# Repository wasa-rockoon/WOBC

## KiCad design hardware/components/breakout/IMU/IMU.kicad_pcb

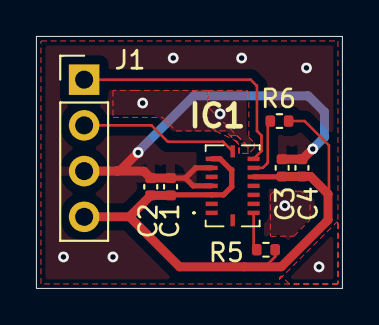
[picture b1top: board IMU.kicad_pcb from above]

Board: 2 copper layers, 17.0 x 14.0 mm, 8 parts (0 on the bottom side), 6 nets.

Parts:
C1, C3: 10μF; C_0402_1005Metric
C2, C4: 100nF; C_0402_1005Metric
IC1: BMI088
J1: Conn_01x04_Pin; PinHeader_1x04_P2.54mm_Vertical
R5, R6: 4.7K; R_0402_1005Metric

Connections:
AD0: IC1.15 (SDO1), R5.1
AD1: IC1.10 (SDO2), R6.1
GND: C1.2, C2.2, C3.2, C4.2, IC1.4 (GNDA), IC1.6 (GNDIO), J1.3
SCL: IC1.8 (SCL/SCK), J1.2
SDA: IC1.9 (SDA/SDI), J1.1
VDD: C1.1, C2.1, C3.1, C4.1, IC1.3 (VDD), IC1.7 (PS), IC1.11 (VDDIO), J1.4, R5.2, R6.2

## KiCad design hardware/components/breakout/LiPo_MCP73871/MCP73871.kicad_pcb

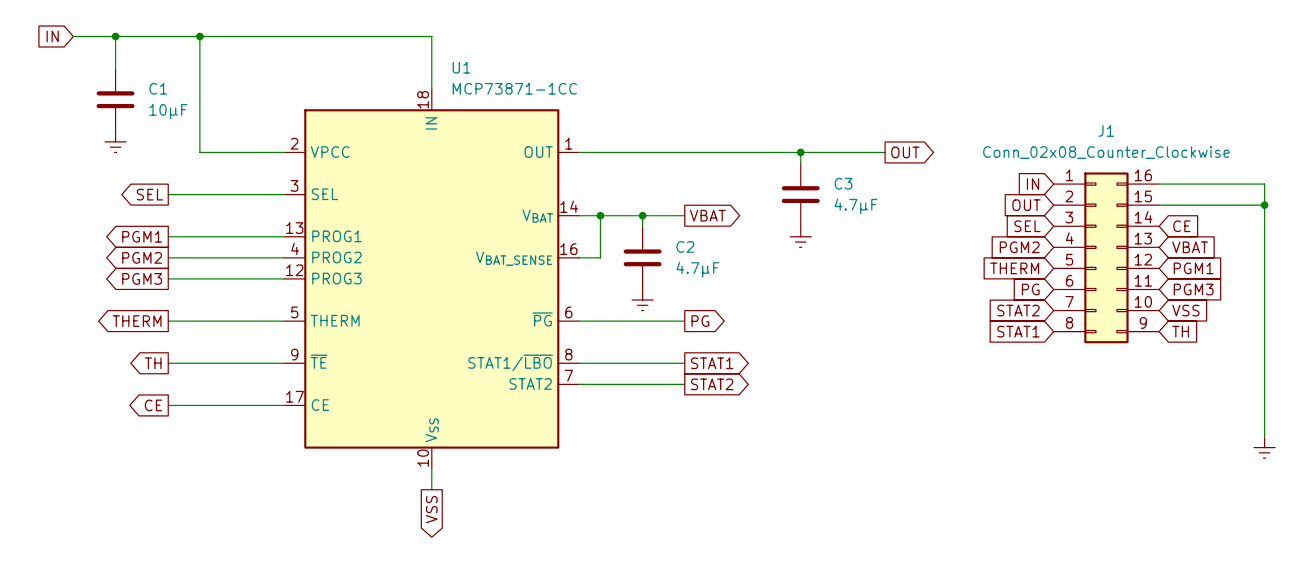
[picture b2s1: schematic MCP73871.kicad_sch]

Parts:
C1: 10μF; C_01005_0402Metric
C2, C3: 4.7μF; C_01005_0402Metric
J1: Conn_02x08_Counter_Clockwise; DIP-16_W10.16mm
U1: MCP73871-1CC; QFN-20-1EP_4x4mm_P0.5mm_EP2.5x2.5mm

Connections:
CE: J1.14, U1.17 (CE)
Earth: C1.2, C2.2, C3.2, J1.15, J1.16
IN: C1.1, J1.1, U1.2 (VPCC), U1.18 (IN), U1.19 (IN)
OUT: C3.1, J1.2, U1.1 (OUT), U1.20 (OUT)
PG: J1.6, U1.6 (~PG)
PGM1: J1.12, U1.13 (PROG1)
PGM2: J1.4, U1.4 (PROG2)
PGM3: J1.11, U1.12 (PROG3)
SEL: J1.3, U1.3 (SEL)
STAT1: J1.8, U1.8 (STAT1/~LBO)
STAT2: J1.7, U1.7 (STAT2)
TH: J1.9, U1.9 (~TE)
THERM: J1.5, U1.5 (THERM)
VBAT: C2.1, J1.13, U1.14 (V_{BAT}), U1.15 (V_{BAT}), U1.16 (V_{BAT_SENSE})
VSS: J1.10, U1.10 (V_{SS}), U1.11 (V_{SS}), U1.21 (V_{SS})

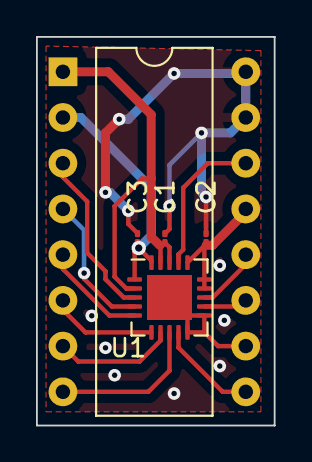
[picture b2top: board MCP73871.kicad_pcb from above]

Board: 2 copper layers, 13.2 x 21.6 mm, 5 parts (0 on the bottom side), 15 nets.

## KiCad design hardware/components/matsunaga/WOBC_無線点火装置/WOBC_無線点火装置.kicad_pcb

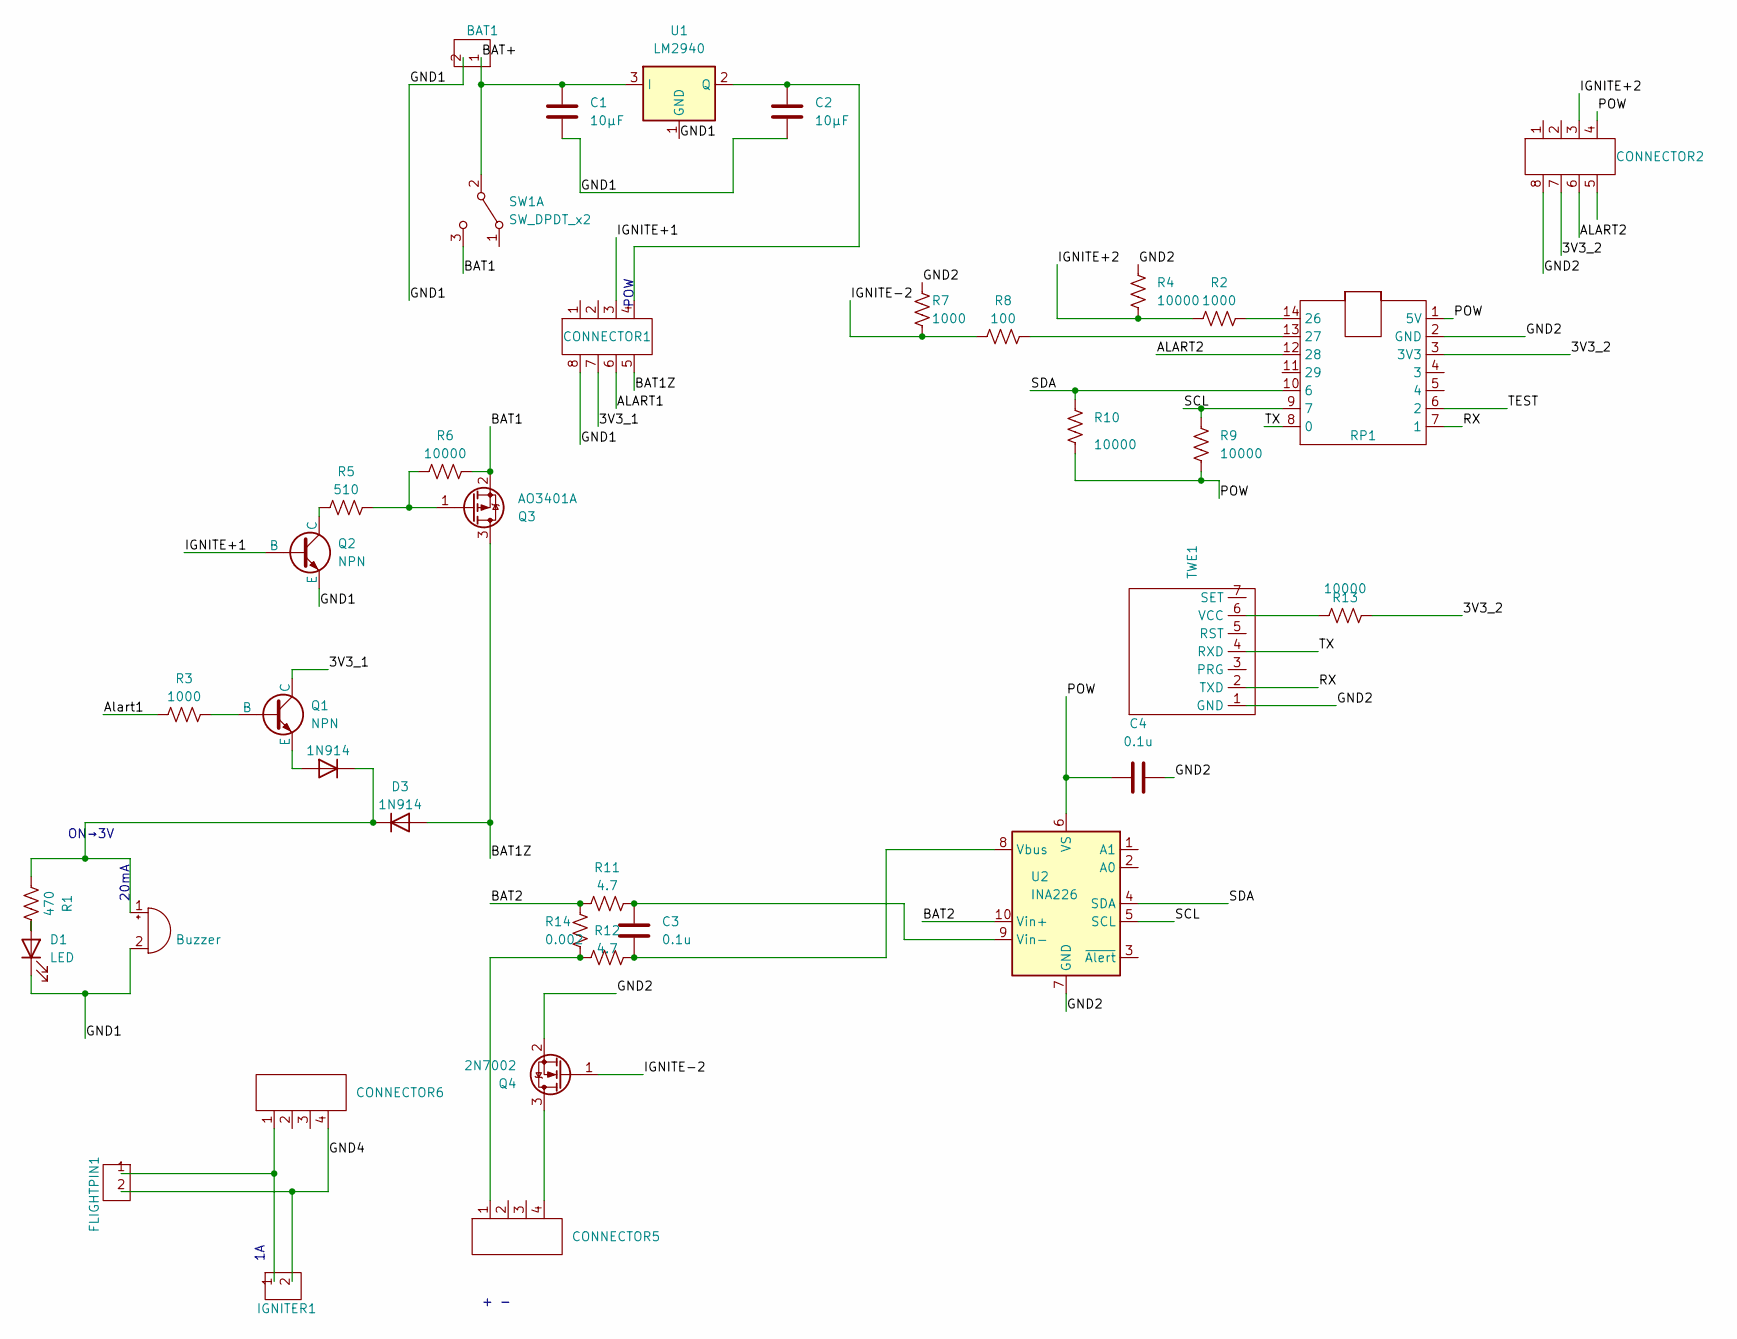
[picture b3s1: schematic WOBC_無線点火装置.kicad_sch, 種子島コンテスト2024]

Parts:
BAT1: 3pin_connector
BZ1: Buzzer; Buzzer_15x7.5RM7.6
C1, C2: 10μF; C_1206_3216Metric_Pad1.33x1.80mm_HandSolder
C3, C4: 0.1u; C_1206_3216Metric_Pad1.33x1.80mm_HandSolder
CONNECTOR1, CONNECTOR2: 8pin_looseconnector
CONNECTOR5, CONNECTOR6: 4pin_looseconnector
D1: LED; SML-D12x1
D2, D3: 1N914; D_DO-35_SOD27_P7.62mm_Horizontal
FLIGHTPIN1: 2pin_connector
IGNITER1: 2pin_connector
Q1, Q2: NPN; npn
Q3: AO3401A; SOT-23
Q4: 2N7002; SOT-23
R1: 470; 30mil
R2, R3, R7: 1000; 1.05K
R4, R6, R9, R10, R13: 10000; 30mil
R5: 510; 1.05K
R8: 100; 30mil
R11, R12: 4.7; 30mil
R14: 0.002
RP1: SeeedXiaoRP2040
SW1: SW_DPDT_x2; SW
TWE1: TWELITE
U1: LM2940; TO-252-3_TabPin2
U2: INA226; VSSOP-10_3x3mm_P0.5mm

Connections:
/3V3_1: CONNECTOR1.7, Q1.1 (C)
/3V3_2: CONNECTOR2.7, R13.1, RP1.3 (3V3)
/ALART1: CONNECTOR1.6
/ALART2: CONNECTOR2.6, RP1.12 (28)
/Alart1: R3.2
/BAT1: Q3.2 (S), R6.1, SW1.3 (C)
/BAT1Z: CONNECTOR1.5, D3.2 (A), Q3.3 (D)
/BAT2: R11.2, R14.1, U2.10 (Vin+)
/BAT+: BAT1.1, C1.1, SW1.2 (B), U1.3 (I)
/GND1: BAT1.2, BZ1.2 (+), C1.2, C2.2, CONNECTOR1.8, D1.1 (K), Q2.3 (E), U1.1 (GND)
/GND2: C4.2, CONNECTOR2.8, Q4.2 (S), R4.2, R7.2, RP1.2 (GND), TWE1.1 (GND), U2.7 (GND)
/GND4: CONNECTOR6.4, FLIGHTPIN1.2, IGNITER1.2
/IGNITE+1: CONNECTOR1.3, Q2.2 (B)
/IGNITE+2: CONNECTOR2.3, R2.2, R4.1
/IGNITE-2: Q4.1 (G), R7.1, R8.2
/POW: C4.1, CONNECTOR2.4, R9.2, R10.2, RP1.1 (5V), U2.6 (VS)
/RX: RP1.7 (1), TWE1.2 (TXD)
/SCL: R9.1, RP1.9 (7), U2.5 (SCL)
/SDA: R10.1, RP1.10 (6), U2.4 (SDA)
/TEST: RP1.6 (2)
/TX: RP1.8 (0), TWE1.4 (RXD)
unnamed: BZ1.1 (-), D2.1 (K), D3.1 (K), R1.1
unnamed: CONNECTOR5.1, R12.2, R14.2
unnamed: CONNECTOR6.1, FLIGHTPIN1.1, IGNITER1.1
unnamed: D1.2 (A), R1.2
unnamed: D2.2 (A), Q1.3 (E)
unnamed: Q1.2 (B), R3.1
unnamed: Q2.1 (C), R5.2
unnamed: Q3.1 (G), R5.1, R6.2
unnamed: CONNECTOR5.4, Q4.3 (D)
unnamed: R2.1, RP1.14 (26)
unnamed: R8.1, RP1.13 (27)
unnamed: R13.2, TWE1.6 (VCC)
unnamed: C2.1, CONNECTOR1.4, U1.2 (Q)
unnamed: C3.2, R12.1, U2.8 (Vbus)
unnamed: C3.1, R11.1, U2.9 (Vin-)

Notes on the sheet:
20mA
POW
ON→3V
+ -

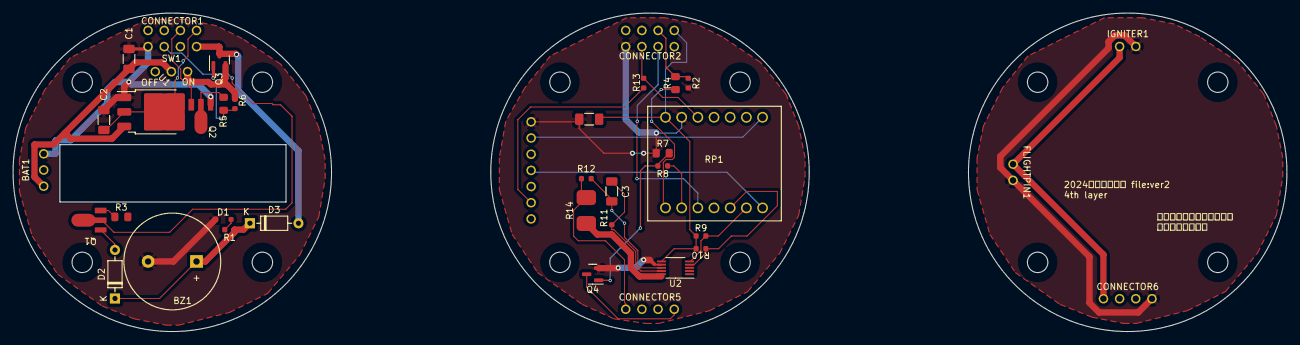
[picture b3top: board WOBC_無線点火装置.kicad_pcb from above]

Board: 2 copper layers, 200.0 x 50.0 mm, 38 parts (0 on the bottom side), 33 nets.

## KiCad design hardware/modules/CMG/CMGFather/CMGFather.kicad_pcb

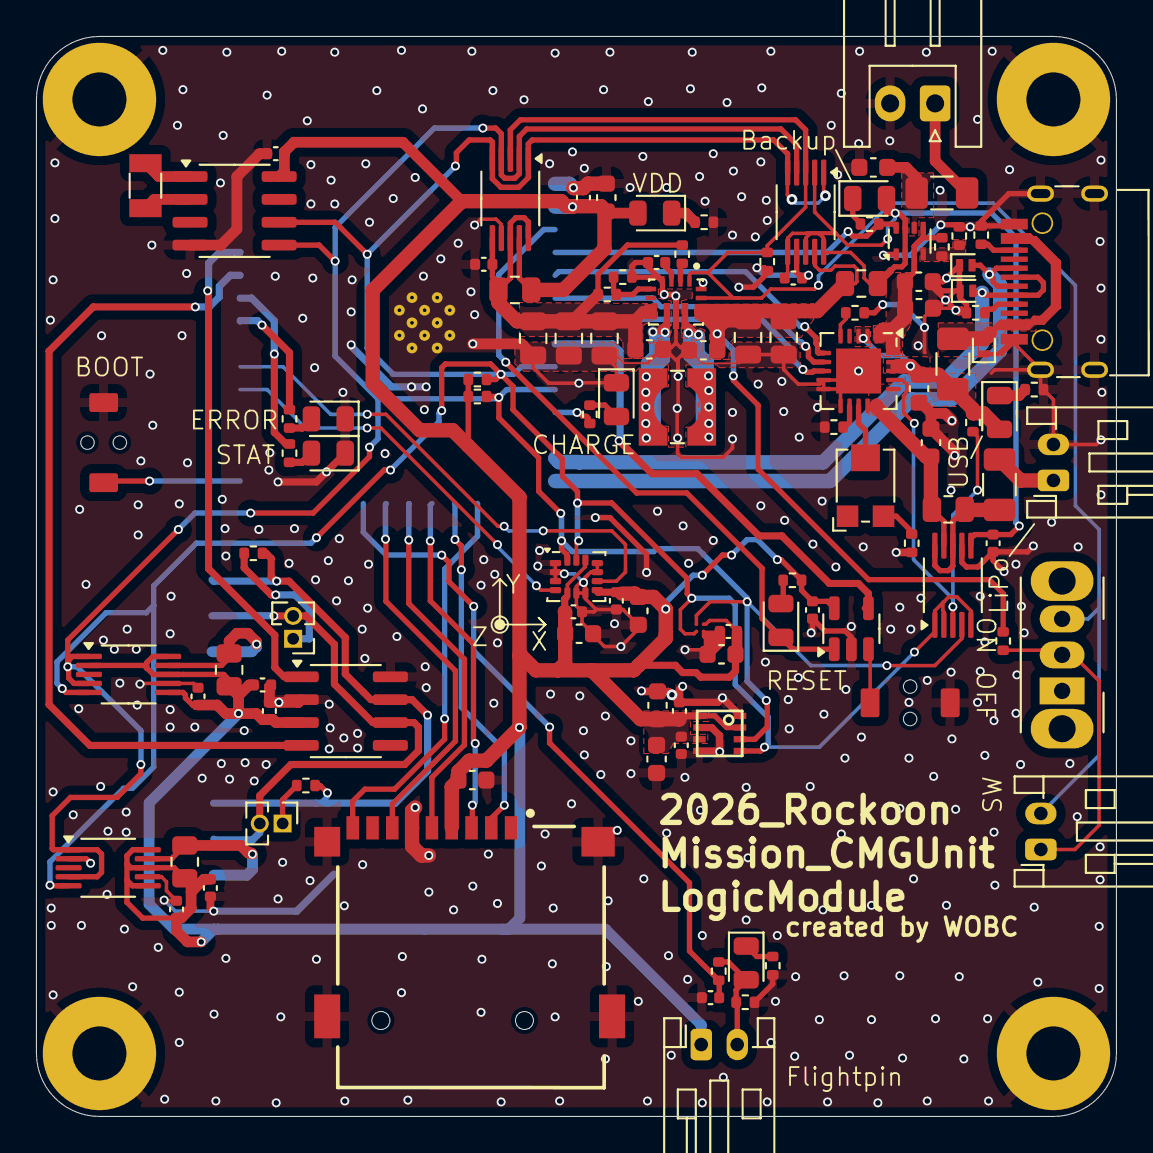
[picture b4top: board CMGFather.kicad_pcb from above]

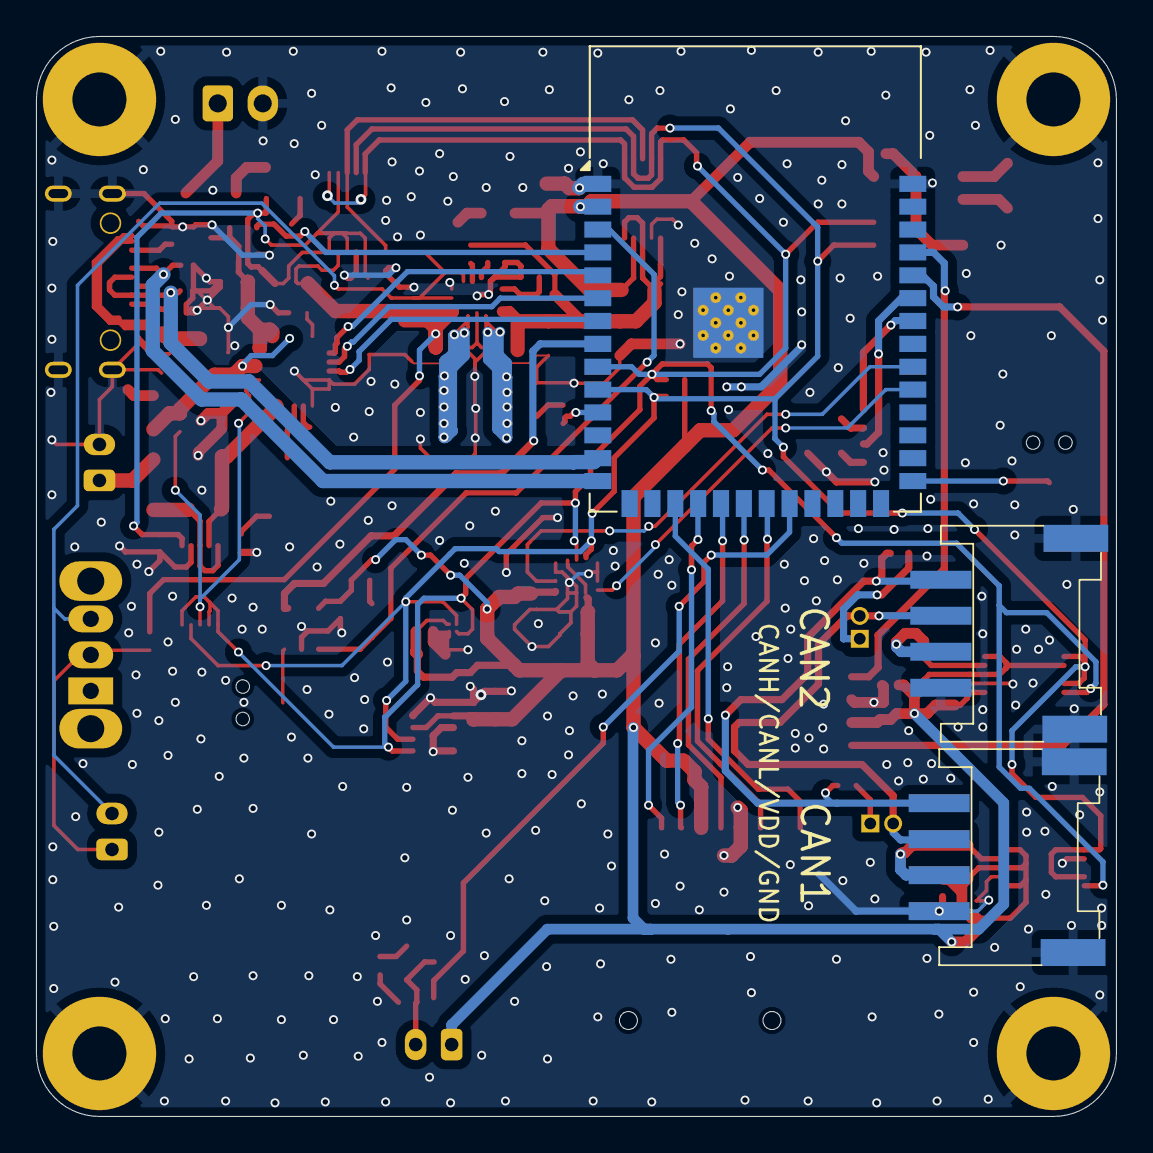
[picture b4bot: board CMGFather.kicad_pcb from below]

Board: 2 copper layers, 60.0 x 60.0 mm, 115 parts (3 on the bottom side), 70 nets.

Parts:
B101: Board_1U_60x60
C201, C308, C309, C310, C312, C313, C314, C315, C501, C504, C506, C602: 10uF; C_0603_1608Metric
C202, C203, C204, C306, C307, C311, C316, C402, C403, C502, C503, C505, C601, C701, C702, C802, C803, C901: 100nF; C_0402_1005Metric
C301, C302, C303, C304, C305: 22uF; C_0805_2012Metric
C401, C404: 10μF; C_0603_1608Metric
D201, D202, D203: 5V; D_SOD-882
D204: ERROR; LED_0805_2012Metric
D205: STAT; LED_0805_2012Metric
D206: RESET; LED_0805_2012Metric
D901: Flightpin; LED_0805_2012Metric
F301, F302, F303: Polyfuse; Fuse_1206_3216Metric
J301: Battery; JST_XH_S2B-XH-A_1x02_P2.50mm_Horizontal
J302: Ext Switch; JST_PH_S2B-PH-K_1x02_P2.00mm_Horizontal
J303: LiPo; JST_PH_S2B-PH-K_1x02_P2.00mm_Horizontal
J701, J801: Jumper; PinHeader_1x02_P1.27mm_Vertical
J702, J802: Conn_01x04_MountingPin; Grove_4P_L_SMD
J901: Flightpin; JST_PH_S2B-PH-K_1x02_P2.00mm_Horizontal
L301: L; L_Wuerth_WE-TPC-3816
LED301: Backup; LED_0805_2012Metric
LED302: VDD; LED_0805_2012Metric
LED303: USB Power; LED_0805_2012Metric
LED304: CHARGE; LED_0805_2012Metric
MICRO_SD601: TF-01A
R201, R202: 5.1k; R_0402_1005Metric
R203, R207, R304, R317, R902: 10k; R_0402_1005Metric
R204, R205, R206, R903: 470; R_0402_1005Metric
R301, R302, R313, R702, R802: 50mΩ; R_0805_2012Metric
R303, R311: 47k; R_0402_1005Metric
R305: 15k; R_0402_1005Metric
R306, R308, R314, R315, R318, R901: 1k; R_0402_1005Metric
R307, R309, R312, R316: 100k; R_0402_1005Metric
R310: 330k; R_0402_1005Metric
R701, R801: 120; R_0402_1005Metric
RV301: 10k; Potentiometer_Bourns_TC33X_Vertical
SW201: RESET_sw; TVAF06-A020B-R
SW202: Boot_sw; TVAF06-A020B-R
SW301: Power Switch; SW_Slide_SPDT_Angled_CK_OS102011MA1Q
U201: ESP32-S3-WROOM-1
U202: TPS3820; SOT-23-5
U203: SN65HVD230; SOIC-8_3.9x4.9mm_P1.27mm
U301: TPS63070RNMR; VREG_TPS63070RNMR
U302: TPS2116DRL; SOT-583-8
U303, U304, U306, U701, U802: INA226; VSSOP-10_3x3mm_P0.5mm
U305: MCP73871-1CC; QFN-20-1EP_4x4mm_P0.5mm_EP2.5x2.5mm
U401: BME280
U501: ICM-42688-P; LGA-14_3x2.5mm_P0.5mm_LayoutBorder3x4y
U502: MMC5603NJL; WLP4_0P82X0P82_MEM-L
U601: PCF8563T; SOIC-8_3.9x4.9mm_P1.27mm
USB201: USB_C_Receptacle_USB2.0; USB_C_TYPEC-301S-ACP16X7
Y601: Crystal; Crystal_SMD_3215-2Pin_3.2x1.5mm

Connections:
/CANH: J702.1, J802.1, R701.2, R801.2, U203.7 (CANH)
/CANL: J701.2, J702.2, J801.2, J802.2, U203.6 (CANL)
/ESP32S3-WROOM-1/CAN_RX: U201.36 (U0RXD/GPIO44/CLK_OUT2), U203.4 (R)
/ESP32S3-WROOM-1/CAN_TX: U201.37 (U0TXD/GPIO43/CLK_OUT1), U203.1 (D)
/ESP32S3-WROOM-1/GPIO4/ADC1_CH3: R306.2, U201.4 (GPIO4/TOUCH4/ADC1_CH3), U302.8 (ST)
/ESP32S3-WROOM-1/GPIO5/ADC1_CH4: U201.5 (GPIO5/TOUCH5/ADC1_CH4), U305.6 (~PG)
/ESP32S3-WROOM-1/GPIO6/ADC1_CH5: U201.6 (GPIO6/TOUCH6/ADC1_CH5), U305.7 (STAT2)
/ESP32S3-WROOM-1/GPIO7/ADC1_CH6: U201.7 (GPIO7/TOUCH7/ADC1_CH6), U305.8 (STAT1/~LBO)
/ESP32S3-WROOM-1/GPIO9/ADC1_CH8: MICRO_SD601.CD1 (CD), U201.17 (GPIO9/TOUCH9/ADC1_CH8/FSPIHD/SUBSPIHD)
/ESP32S3-WROOM-1/GPIO10/ADC1_CH9: MICRO_SD601.2 (CD/DAT3), U201.18 (GPIO10/TOUCH10/ADC1_CH9/FSPICS0/FSPIIO4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)
/ESP32S3-WROOM-1/GPIO11: MICRO_SD601.3 (CMD), U201.19 (GPIO11/TOUCH11/ADC2_CH0/FSPID/FSPIIO5/S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)
/ESP32S3-WROOM-1/GPIO12: MICRO_SD601.5 (CLK), U201.20 (GPIO12/TOUCH12/ADC2_CH1/FSPICLK/FSPIIO6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)
/ESP32S3-WROOM-1/GPIO13: MICRO_SD601.7 (DAT0), U201.21 (GPIO13/TOUCH13/ADC2_CH2/FSPIQ/FSPIIO7/S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)
/ESP32S3-WROOM-1/GPIO14: C901.1, R901.1, U201.22 (GPIO14/TOUCH14/ADC2_CH3/FSPIWP/FSPIDQS/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)
/ESP32S3-WROOM-1/GPIO18: R318.2, U201.11 (GPIO18/U1RXD/ADC2_CH7/CLK_OUT3)
/ESP32S3-WROOM-1/USB_D+: D202.2 (A2), U201.14 (GPIO20/U1CTS/ADC2_CH9/CLK_OUT1/USB_D+), USB201.A6 (D+), USB201.B6 (D+)
/ESP32S3-WROOM-1/USB_D-: D203.2 (A2), U201.13 (GPIO19/U1RTS/ADC2_CH8/CLK_OUT2/USB_D-), USB201.A7 (D-), USB201.B7 (D-)
/ESP32S3-WROOM-1/WDI: U201.8 (GPIO15/U0RTS/ADC2_CH4/XTAL_32K_P), U202.4 (WDI)
/I2C_SCL: R203.2, U201.9 (GPIO16/U0CTS/ADC2_CH5/XTAL_32K_N), U303.1 (A1), U303.5 (SCL), U304.1 (A1), U304.5 (SCL), U306.1 (A1), U306.2 (A0), U306.5 (SCL), U401.4 (SCK), U501.13 (AP_SCL/AP_SCLK), U502.A2 (SCL), U601.6 (SCL), U701.5 (SCL), U802.5 (SCL)
/I2C_SDA: R207.2, U201.10 (GPIO17/U1TXD/ADC2_CH6), U303.4 (SDA), U304.2 (A0), U304.4 (SDA), U306.4 (SDA), U401.3 (SDI), U501.14 (AP_SDA/AP_SDIO/AP_SDI), U502.B2 (SDA), U601.5 (SDA), U701.1 (A1), U701.4 (SDA), U802.1 (A1), U802.4 (SDA)
/INT1: U201.31 (GPIO38/FSPIWP/SUBSPIWP), U501.4 (INT1/INT)
/INT2: U201.32 (MTCK/GPIO39/CLK_OUT3/SUBSPICS1), U501.9 (INT2/FSYNC/CLKIN)
/LiPoPower/MCP73871_IN: C313.1, F302.2, LED303.2 (A), R312.1, U305.2 (VPCC), U305.3 (SEL), U305.18 (IN), U305.19 (IN)
/LiPoPower/PROG: RV301.2, U305.13 (PROG1)
/LiPoPower/VDD_BUS: C303.1, C304.1, C305.1, C307.1, C309.1, R302.1, R303.2, R307.1, U301.7_8 (VOUT), U304.6 (VS), U304.8 (Vbus), U304.10 (Vin+)
GND: B101.GND, C201.1, C202.2, C203.1, C204.1, C301.2, C302.2, C303.2, C304.2, C305.2, C306.2, C307.2, C308.2, C309.2, C310.2, C311.2, C312.2, C313.2, C314.2, C315.2, C316.2, C401.2, C402.2, C403.2, C404.2, C501.1, C502.1, C503.2, C504.2, C505.2, C506.2, C601.1, C602.2, C701.1, C702.1, C802.1, C803.1, C901.2, D201.1 (A1), D202.1 (A1), D203.1 (A1), D204.1 (K), D205.1 (K), J301.2, J303.2, J702.4, J702.MP (MountPin), J802.4, J802.MP (MountPin), LED304.1 (K), MICRO_SD601.6 (VSS), MICRO_SD601.MP1 (SHIELD), MICRO_SD601.MP2 (SHIELD), MICRO_SD601.MP3 (SHIELD), MICRO_SD601.MP4 (SHIELD), R201.2, R202.2, R305.1, R308.2, R310.2, R311.1, R314.2, R315.2, R316.2, R317.2, R902.1, R903.2, SW201.2, SW202.2, U201.1 (GND), U201.40 (GND), U201.41 (GND), U202.2 (GND), U203.2 (GND), U203.8 (Rs), U301.4 (GND), U301.10 (PGND), U301.15 (VSEL), U302.1 (GND), U303.7 (GND), U304.7 (GND), U305.9 (~TE), U305.10 (V_{SS}), U305.11 (V_{SS}), U305.21 (V_{SS}), U306.7 (GND), U401.1 (GND), U401.5 (SDO), U401.7 (GND), U501.1 (AP_SDO/AP_AD0), U501.2 (RESV), U501.3 (RESV), U501.6 (GND), U501.7 (RESV), U501.10 (RESV), U501.11 (RESV), U502.A1 (VSA), U601.4 (VSS), U701.2 (A0), U701.7 (GND), U802.7 (GND), USB201.A1 (GND), USB201.A12 (GND), USB201.B1 (GND), USB201.B12 (GND), USB201.S1 (SHIELD)
unnamed: D204.2 (A), R204.2
unnamed: D205.2 (A), R205.2
unnamed: D206.2 (A), R206.2
unnamed: D901.2 (A), J901.2, R901.2, R902.2
unnamed: D901.1 (K), R903.1
unnamed: F301.1, J301.1
unnamed: J302.1, R304.1, SW301.2 (B)
unnamed: J302.2, R310.1, SW301.3 (C), U301.1 (PS/SYNC), U301.14 (EN), U303.3 (~Alert), U304.3 (~Alert)
unnamed: F303.2, J303.1
unnamed: J701.1, R701.1
unnamed: J702.3, R702.2, U701.9 (Vin-)
unnamed: J801.1, R801.1
unnamed: J802.3, R802.2, U802.9 (Vin-)
unnamed: LED301.1 (K), R306.1
unnamed: LED302.1 (K), R308.1
unnamed: LED303.1 (K), R314.1
unnamed: LED304.2 (A), R318.1
unnamed: R315.1, RV301.3
unnamed: SW202.1, U201.27 (GPIO0/BOOT)
unnamed: R204.1, U201.34 (MTDI/GPIO41/CLK_OUT1)
unnamed: R205.1, U201.35 (MTMS/GPIO42)
unnamed: SW201.1, U202.3 (MR)
unnamed: R303.1, R305.2, U301.5 (FB)
unnamed: L301.1, U301.11 (L1)
unnamed: L301.2, U301.9 (L2)
unnamed: R307.2, U301.2 (PG)
unnamed: C311.1, U301.3 (VAUX)
unnamed: C301.1, C302.1, C310.1, R301.2, R304.2, U301.12_13 (VIN), U303.9 (Vin-)
unnamed: C312.1, C315.1, R309.1, U302.3 (VIN1), U302.5 (MODE), U305.1 (OUT), U305.20 (OUT)
unnamed: R309.2, R311.2, U302.4 (PR1)
unnamed: C308.1, F301.2, U302.6 (VIN2)
unnamed: R312.2, U305.17 (CE), U306.3 (~Alert)
unnamed: R316.1, U305.12 (PROG3)
unnamed: R317.1, U305.5 (THERM)
unnamed: C314.1, R313.1, U305.14 (V_{BAT}), U305.15 (V_{BAT}), U305.16 (V_{BAT_SENSE}), U306.9 (Vin-)
unnamed: F303.1, R313.2, U306.8 (Vbus), U306.10 (Vin+)
unnamed: U601.1 (OSCI), Y601.1
unnamed: U601.2 (OSCO), Y601.2
unnamed: R201.1, USB201.A5 (CC1)
unnamed: R202.1, USB201.B5 (CC2)
RESET: D206.1 (K), U201.3 (EN), U202.1 (RESET)
VBUS: D201.2 (A2), F302.1, USB201.A4 (VBUS), USB201.A9 (VBUS), USB201.B4 (VBUS), USB201.B9 (VBUS)
VDD: C201.2, C202.1, C203.2, C204.2, C401.1, C402.1, C403.1, C404.1, C501.2, C502.2, C503.1, C504.1, C505.1, C506.1, C601.2, C602.1, C701.2, C702.2, C802.2, C803.2, J901.1, LED302.2 (A), MICRO_SD601.4 (VDD), R203.1, R206.1, R207.1, R302.2, R702.1, R802.1, U201.2 (3V3), U202.5 (VDD), U203.3 (VCC), U304.9 (Vin-), U401.2 (CSB), U401.6 (VDDIO), U401.8 (VDD), U501.5 (VDDIO), U501.8 (VDD), U501.12 (AP_CS), U502.B1 (VDD), U601.8 (VDD), U701.6 (VS), U701.8 (Vbus), U701.10 (Vin+), U802.2 (A0), U802.6 (VS), U802.8 (Vbus), U802.10 (Vin+)
VPP: C306.1, C316.1, LED301.2 (A), R301.1, U302.2 (VOUT), U302.7 (VOUT), U303.2 (A0), U303.6 (VS), U303.8 (Vbus), U303.10 (Vin+), U306.6 (VS)
